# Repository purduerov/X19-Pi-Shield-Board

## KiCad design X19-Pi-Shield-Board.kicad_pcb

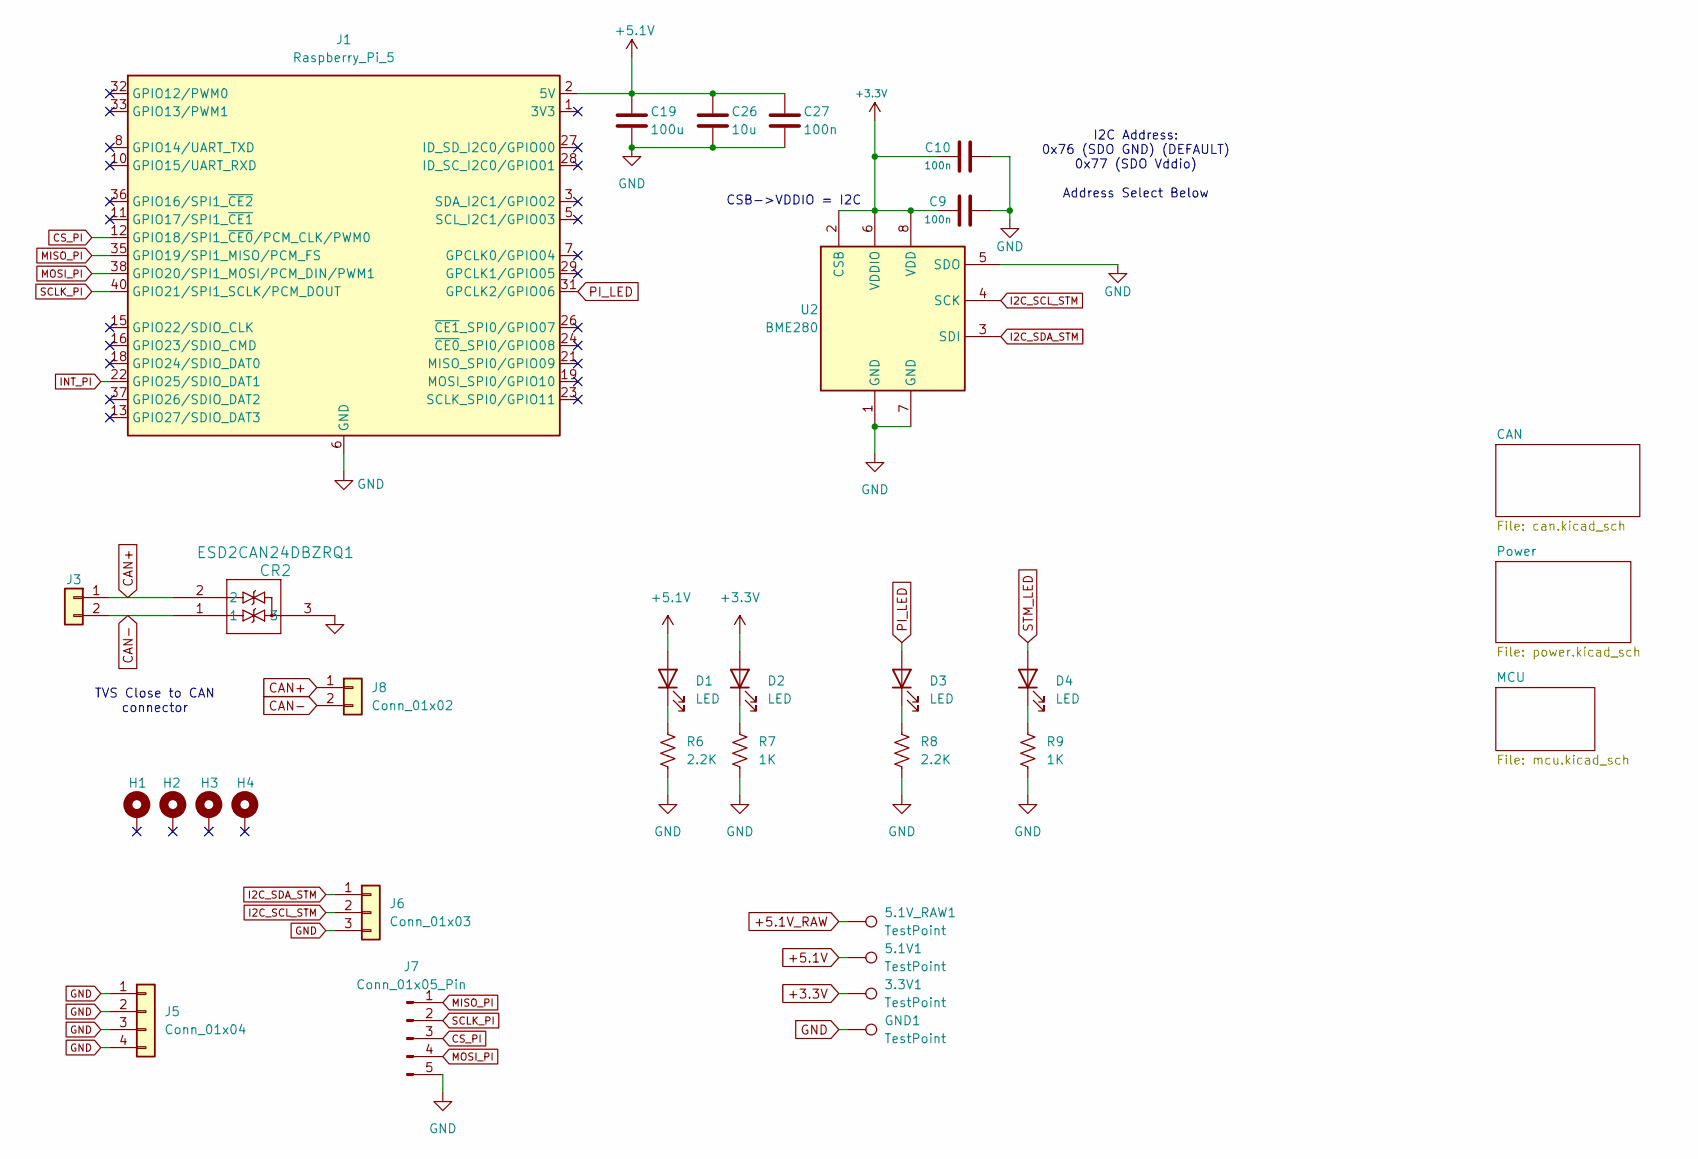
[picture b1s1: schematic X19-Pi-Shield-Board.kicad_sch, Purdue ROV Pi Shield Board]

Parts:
3.3V1, 5.1V1, 5.1V_RAW1: TestPoint; TestPoint_Pad_D2.5mm
C9, C10, C27: 100n; C_0603_1608Metric_Pad1.08x0.95mm_HandSolder
C19: 100u; PCAP_6.3x5.8-ELECT_NCA-M
C26: 10u; C_0603_1608Metric_Pad1.08x0.95mm_HandSolder
CR2: ESD2CAN24DBZRQ1; SOT-23_DBZ_TEX-M
D1, D2, D3, D4: LED; LED_0805_2012Metric_Pad1.15x1.40mm_HandSolder
GND1: TestPoint; TestPoint_Pad_D2.5mm
H1, H2, H3, H4: MountingHole_Pad; MountingHole_3.2mm_M3
J1: Raspberry_Pi_5; PinSocket_2x20_P2.54mm_Vertical
J3: Conn_01x02; CONN_SD-43650-001_02_MOL
J5: Conn_01x04; PinHeader_1x04_P2.54mm_Vertical
J6: Conn_01x03; PinHeader_1x03_P2.54mm_Vertical
J7: Conn_01x05_Pin; PinHeader_1x05_P2.54mm_Vertical
J8: Conn_01x02; PinHeader_1x02_P2.54mm_Vertical
R6, R8: 2.2K; R_0603_1608Metric_Pad0.98x0.95mm_HandSolder
R7, R9: 1K; R_0603_1608Metric_Pad0.98x0.95mm_HandSolder
U2: BME280; Bosch_LGA-8_2.5x2.5mm_P0.65mm_ClockwisePinNumbering

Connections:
+3.3V: 3.3V1.1 (1_1), C9.1, C10.2, D2.2 (A), U2.2 (CSB), U2.6 (VDDIO), U2.8 (VDD); also elsewhere on the board
+5.1V: 5.1V1.1 (1_1), C19.1, C26.1, C27.1, D1.2 (A), J1.2 (5V), J1.4 (5V); also elsewhere on the board
+5.1V_RAW: 5.1V_RAW1.1 (1_1); also elsewhere on the board
CAN+: CR2.2, J3.1, J8.1; also elsewhere on the board
CAN-: CR2.1, J3.2, J8.2; also elsewhere on the board
CS_PI: J1.12 (GPIO18/SPI1_~CE0/PCM_CLK/PWM0), J7.3; also elsewhere on the board
GND: C9.2, C10.1, C19.2, C26.2, C27.2, CR2.3, GND1.1 (1_1), J1.6 (GND), J1.9 (GND), J1.14 (GND), J1.20 (GND), J1.25 (GND), J1.30 (GND), J1.34 (GND), J1.39 (GND), J5.1, J5.2, J5.3, J5.4, J6.3, J7.5, R6.2, R7.2, R8.2, R9.2, U2.1 (GND), U2.5 (SDO), U2.7 (GND); also elsewhere on the board
I2C_SCL_STM: J6.2, U2.4 (SCK); also elsewhere on the board
I2C_SDA_STM: J6.1, U2.3 (SDI); also elsewhere on the board
INT_PI: J1.22 (GPIO25/SDIO_DAT1); also elsewhere on the board
MISO_PI: J1.35 (GPIO19/SPI1_MISO/PCM_FS), J7.1; also elsewhere on the board
MOSI_PI: J1.38 (GPIO20/SPI1_MOSI/PCM_DIN/PWM1), J7.4; also elsewhere on the board
unnamed: D1.1 (K), R6.1
unnamed: D2.1 (K), R7.1
unnamed: D3.1 (K), R8.1
unnamed: D4.1 (K), R9.1
PI_LED: D3.2 (A), J1.31 (GPCLK2/GPIO06)
SCLK_PI: J1.40 (GPIO21/SPI1_SCLK/PCM_DOUT), J7.2; also elsewhere on the board
STM_LED: D4.2 (A); also elsewhere on the board

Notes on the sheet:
CSB->VDDIO = I2C
TVS Close to CAN connector
I2C Address: 0x76 (SDO GND) (DEFAULT) 0x77 (SDO Vddio) Address Select Below

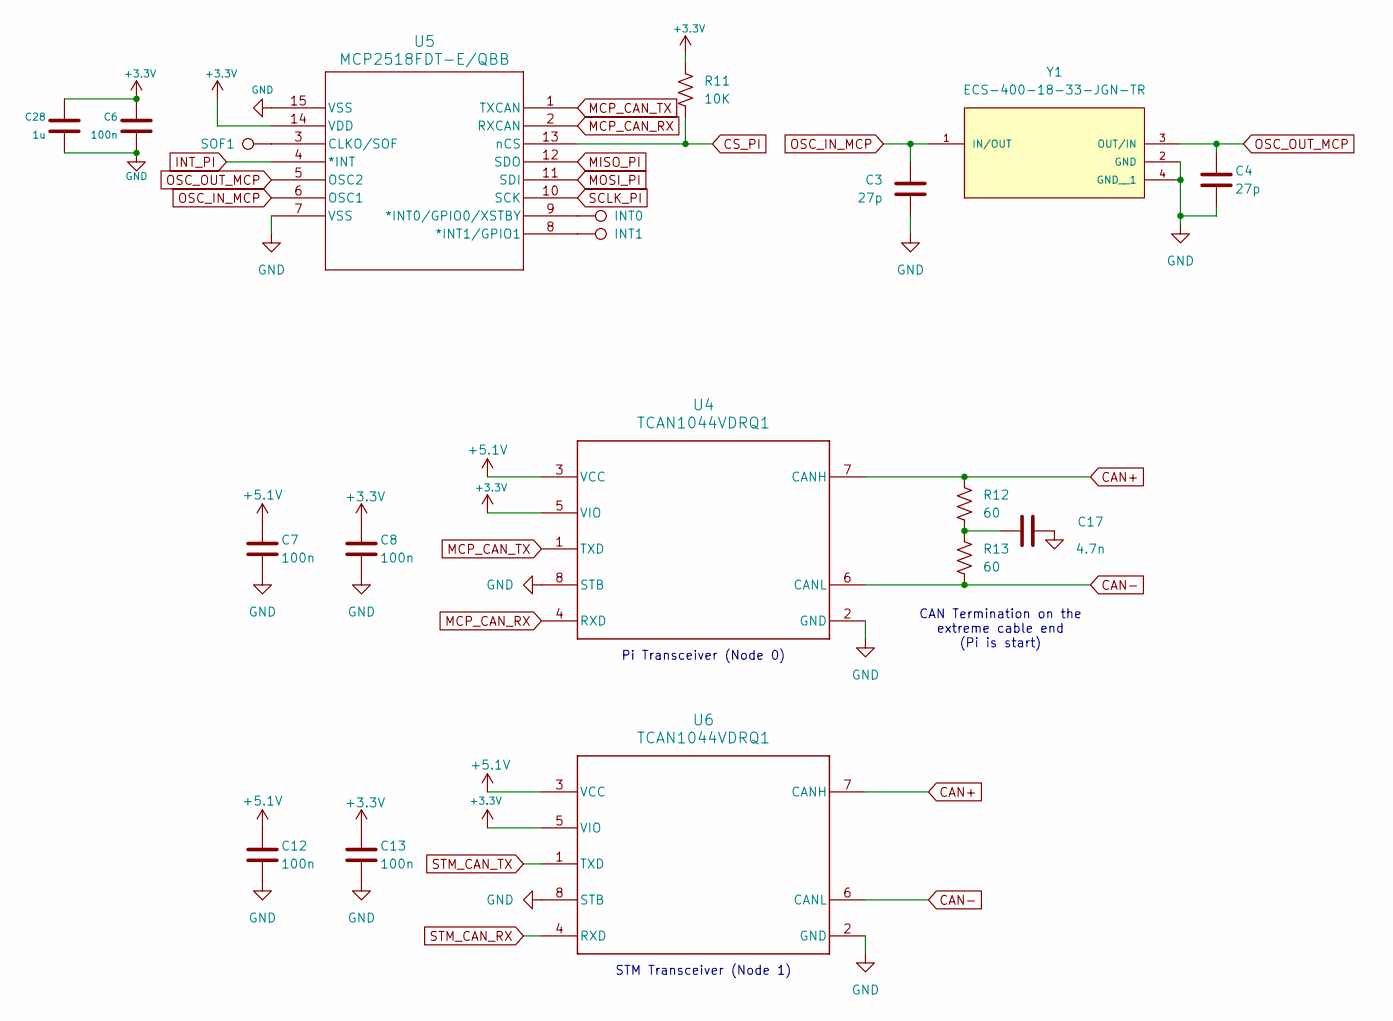
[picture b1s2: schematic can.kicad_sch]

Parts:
C3, C4: 27p; C_0603_1608Metric_Pad1.08x0.95mm_HandSolder
C6, C7, C8, C12, C13: 100n; C_0603_1608Metric_Pad1.08x0.95mm_HandSolder
C17: 4.7n; C_0603_1608Metric_Pad1.08x0.95mm_HandSolder
C28: 1u; C_0603_1608Metric_Pad1.08x0.95mm_HandSolder
INT0, INT1: TestPoint; TestPoint_Pad_D1.5mm
R11: 10K; R_0603_1608Metric_Pad0.98x0.95mm_HandSolder
R12, R13: 60; R_0603_1608Metric_Pad0.98x0.95mm_HandSolder
SOF1: TestPoint; TestPoint_Pad_D1.5mm
U4, U6: TCAN1044VDRQ1; D0008A-IPC_A
U5: MCP2518FDT-E/QBB; VDFN14_QBB_MCH-M
Y1: ECS-400-18-33-JGN-TR; XTAL_ECS-400-18-33-JGN-TR

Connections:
+3.3V: C6.1, C8.1, C13.1, C28.1, R11.1, U4.5 (VIO), U5.14 (VDD), U6.5 (VIO); also elsewhere on the board
+5.1V: C7.1, C12.1, U4.3 (VCC), U6.3 (VCC); also elsewhere on the board
CAN+: R12.1, U4.7 (CANH), U6.7 (CANH); also elsewhere on the board
CAN-: R13.2, U4.6 (CANL), U6.6 (CANL); also elsewhere on the board
CS_PI: R11.2, U5.13 (nCS); also elsewhere on the board
GND: C3.1, C4.2, C6.2, C7.2, C8.2, C12.2, C13.2, C17.2, C28.2, U4.2 (GND), U4.8 (STB), U5.7 (VSS), U5.15 (VSS), U6.2 (GND), U6.8 (STB), Y1.2 (GND), Y1.4 (GND__1); also elsewhere on the board
INT_PI: U5.4 (*INT); also elsewhere on the board
MCP_CAN_RX: U4.4 (RXD), U5.2 (RXCAN)
MCP_CAN_TX: U4.1 (TXD), U5.1 (TXCAN)
MISO_PI: U5.12 (SDO); also elsewhere on the board
MOSI_PI: U5.11 (SDI); also elsewhere on the board
unnamed: C17.1, R12.2, R13.1
unnamed: INT0.1 (1_1), U5.9 (*INT0/GPIO0/XSTBY)
unnamed: INT1.1 (1_1), U5.8 (*INT1/GPIO1)
unnamed: SOF1.1 (1_1), U5.3 (CLKO/SOF)
OSC_IN_MCP: C3.2, U5.6 (OSC1), Y1.1 (IN/OUT)
OSC_OUT_MCP: C4.1, U5.5 (OSC2), Y1.3 (OUT/IN)
SCLK_PI: U5.10 (SCK); also elsewhere on the board
STM_CAN_RX: U6.4 (RXD); also elsewhere on the board
STM_CAN_TX: U6.1 (TXD); also elsewhere on the board

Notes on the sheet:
CAN Termination on the extreme cable end (Pi is start)
Pi Transceiver (Node 0)
STM Transceiver (Node 1)

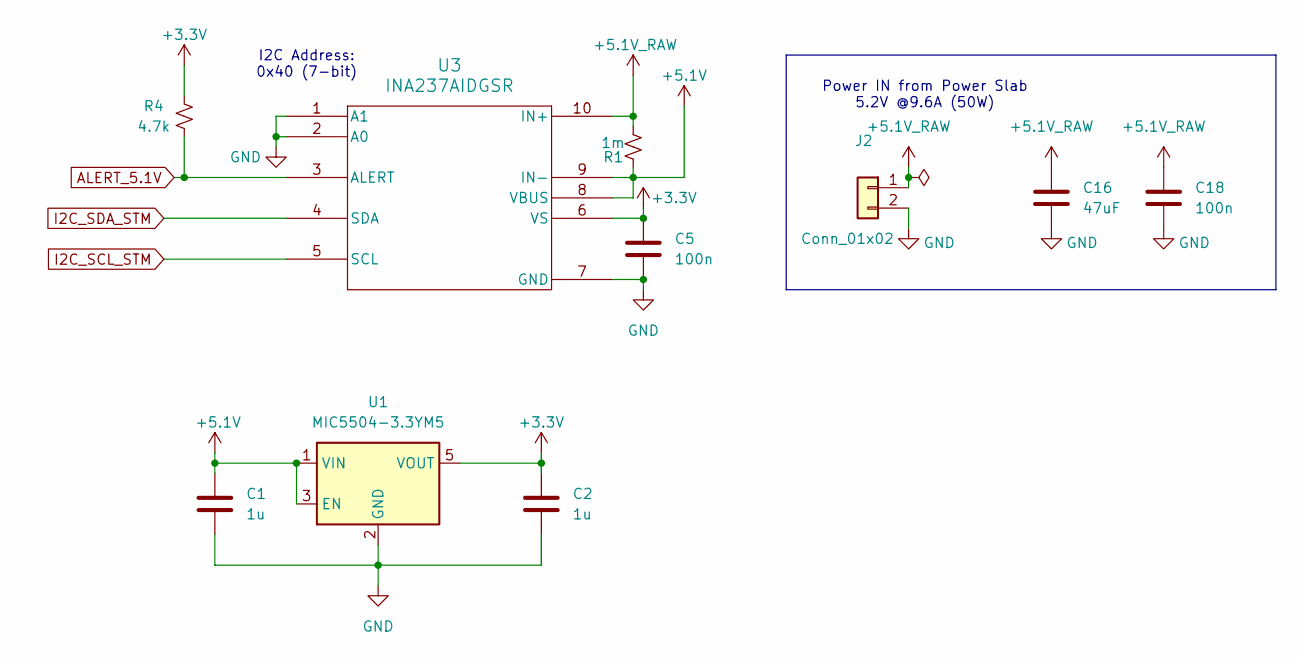
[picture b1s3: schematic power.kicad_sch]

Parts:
C1, C2: 1u; C_0603_1608Metric_Pad1.08x0.95mm_HandSolder
C5, C18: 100n; C_0603_1608Metric_Pad1.08x0.95mm_HandSolder
C16: 47uF; C_1210_3225Metric_Pad1.33x2.70mm_HandSolder
J2: Conn_01x02; CONN_SD-43650-001_02_MOL
R1: 1m; R_1206_3216Metric_Pad1.30x1.75mm_HandSolder
R4: 4.7k; R_0603_1608Metric_Pad0.98x0.95mm_HandSolder
U1: MIC5504-3.3YM5; SOT-23-5
U3: INA237AIDGSR; VSSOP_IDGSR_TEX-M

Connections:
+3.3V: C2.1, C5.1, R4.2, U1.5 (VOUT), U3.6 (VS); also elsewhere on the board
+5.1V: C1.1, R1.1, U1.1 (VIN), U1.3 (EN), U3.8 (VBUS), U3.9 (IN-); also elsewhere on the board
+5.1V_RAW: C16.1, C18.1, J2.1, R1.2, U3.10 (IN+); also elsewhere on the board
ALERT_5.1V: R4.1, U3.3 (ALERT); also elsewhere on the board
GND: C1.2, C2.2, C5.2, C16.2, C18.2, J2.2, U1.2 (GND), U3.1 (A1), U3.2 (A0), U3.7 (GND); also elsewhere on the board
I2C_SCL_STM: U3.5 (SCL); also elsewhere on the board
I2C_SDA_STM: U3.4 (SDA); also elsewhere on the board

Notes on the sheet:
I2C Address: 0x40 (7-bit)
Power IN from Power Slab 5.2V @9.6A (50W)

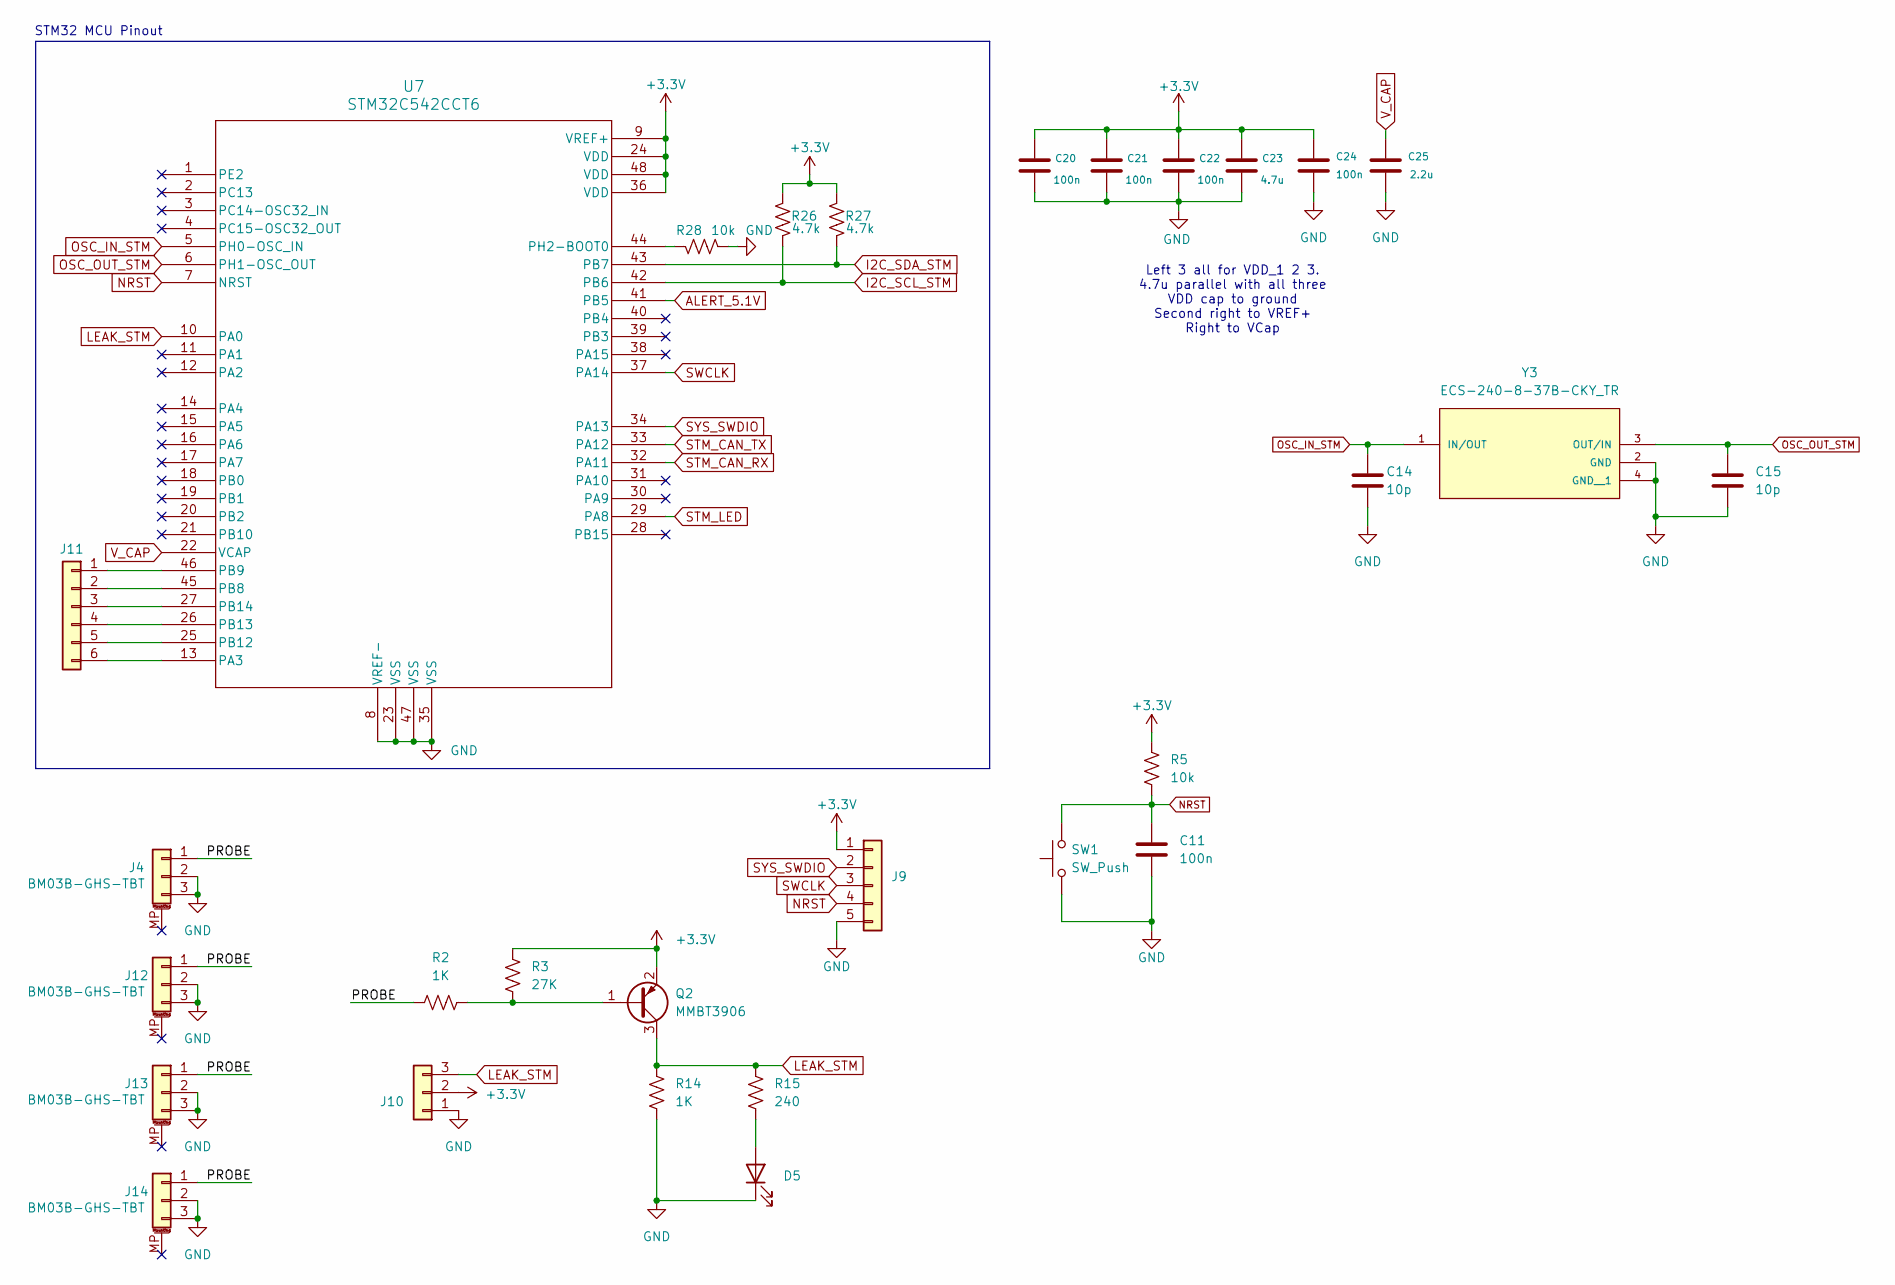
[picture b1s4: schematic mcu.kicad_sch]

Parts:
C11, C20, C21, C22, C24: 100n; C_0603_1608Metric_Pad1.08x0.95mm_HandSolder
C14, C15: 10p; C_0603_1608Metric_Pad1.08x0.95mm_HandSolder
C23: 4.7u; C_0603_1608Metric_Pad1.08x0.95mm_HandSolder
C25: 2.2u; C_0603_1608Metric_Pad1.08x0.95mm_HandSolder
D5: LED; LED_0805_2012Metric_Pad1.15x1.40mm_HandSolder
J4, J12, J13, J14: BM03B-GHS-TBT; JST_GH_BM03B-GHS-TBT_1x03-1MP_P1.25mm_Vertical
J9: Conn_01x05; PinHeader_1x05_P2.54mm_Vertical
J10: Conn_01x03; PinHeader_1x03_P2.54mm_Vertical
J11: Conn_01x06; PinHeader_1x06_P2.54mm_Vertical
Q2: MMBT3906; SOT-23
R2, R14: 1K; R_0603_1608Metric_Pad0.98x0.95mm_HandSolder
R3: 27K; R_0603_1608Metric_Pad0.98x0.95mm_HandSolder
R5, R28: 10k; R_0603_1608Metric_Pad0.98x0.95mm_HandSolder
R15: 240; R_0603_1608Metric_Pad0.98x0.95mm_HandSolder
R26, R27: 4.7k; R_0603_1608Metric_Pad0.98x0.95mm_HandSolder
SW1: SW_Push; SW_FSM2JMTR_TEC-M
U7: STM32C542CCT6; LQFP48-7X7-M
Y3: ECS-240-8-37B-CKY_TR; XTAL_ECS-160-9-37-CKM-TR

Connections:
+3.3V: C20.1, C21.1, C22.1, C23.1, C24.1, J9.1, J10.2, Q2.2 (E), R3.1, R5.1, R26.2, R27.2, U7.9 (VREF+), U7.24 (VDD), U7.36 (VDD), U7.48 (VDD); also elsewhere on the board
/MCU/PROBE: J4.1, J12.1, J13.1, J14.1, R2.1
ALERT_5.1V: U7.41 (PB5); also elsewhere on the board
GND: C11.2, C14.1, C15.2, C20.2, C21.2, C22.2, C23.2, C24.2, C25.2, D5.1 (K), J4.2, J4.3, J9.5, J10.1, J12.2, J12.3, J13.2, J13.3, J14.2, J14.3, R14.2, R28.1, SW1.1, U7.8 (VREF-), U7.23 (VSS), U7.35 (VSS), U7.47 (VSS), Y3.2 (GND), Y3.4 (GND__1); also elsewhere on the board
I2C_SCL_STM: R26.1, U7.42 (PB6); also elsewhere on the board
I2C_SDA_STM: R27.1, U7.43 (PB7); also elsewhere on the board
LEAK_STM: J10.3, Q2.3 (C), R14.1, R15.1, U7.10 (PA0)
NRST: C11.1, J9.4, R5.2, SW1.2, U7.7 (NRST)
unnamed: D5.2 (A), R15.2
unnamed: J11.1, U7.46 (PB9)
unnamed: J11.2, U7.45 (PB8)
unnamed: J11.3, U7.27 (PB14)
unnamed: J11.4, U7.26 (PB13)
unnamed: J11.5, U7.25 (PB12)
unnamed: J11.6, U7.13 (PA3)
unnamed: Q2.1 (B), R2.2, R3.2
unnamed: R28.2, U7.44 (PH2-BOOT0)
OSC_IN_STM: C14.2, U7.5 (PH0-OSC_IN), Y3.1 (IN/OUT)
OSC_OUT_STM: C15.1, U7.6 (PH1-OSC_OUT), Y3.3 (OUT/IN)
STM_CAN_RX: U7.32 (PA11); also elsewhere on the board
STM_CAN_TX: U7.33 (PA12); also elsewhere on the board
STM_LED: U7.29 (PA8); also elsewhere on the board
SWCLK: J9.3, U7.37 (PA14)
SYS_SWDIO: J9.2, U7.34 (PA13)
V_CAP: C25.1, U7.22 (VCAP)

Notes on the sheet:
STM32 MCU Pinout
Left 3 all for VDD_1 2 3. 4.7u parallel with all three VDD cap to ground Second right to VREF+ Right to VCap

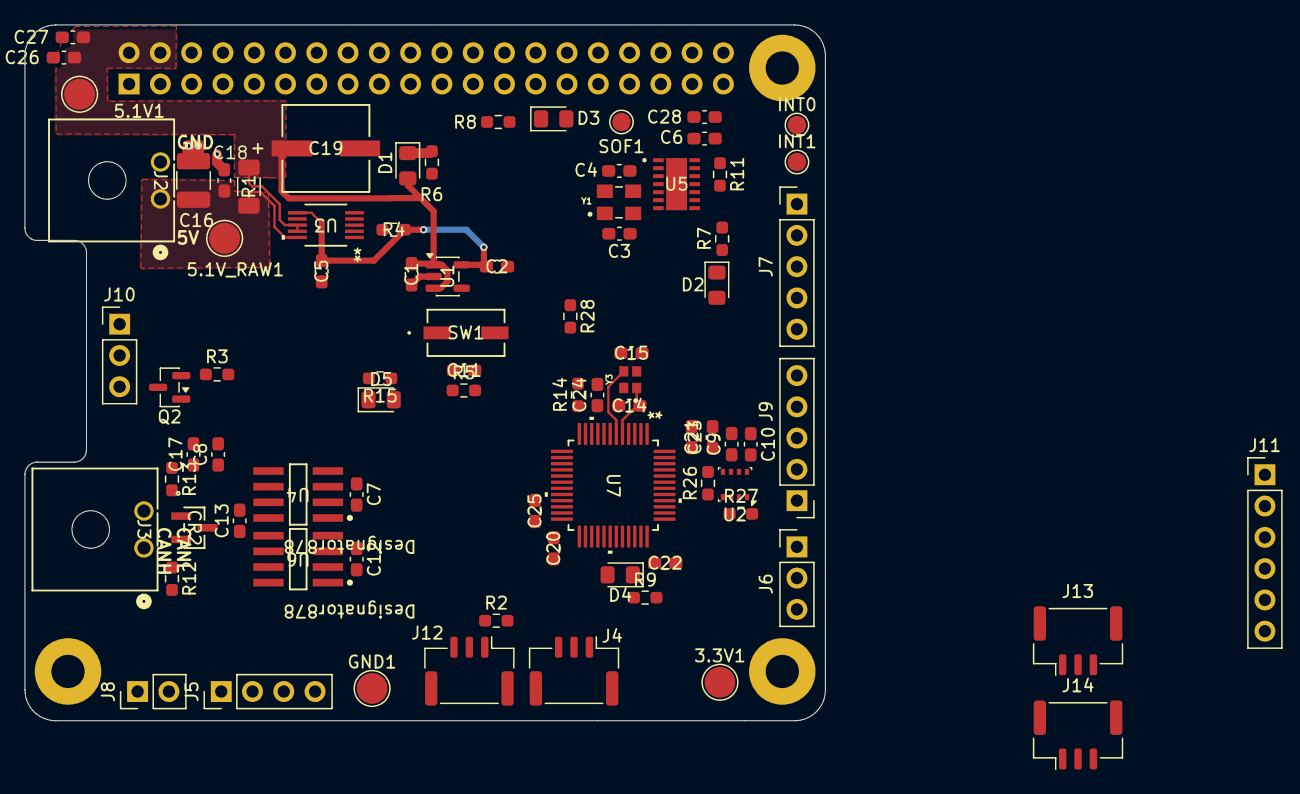
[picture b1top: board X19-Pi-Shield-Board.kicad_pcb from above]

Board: 4 copper layers, 65.0 x 56.5 mm, 86 parts (1 on the bottom side), 47 nets.

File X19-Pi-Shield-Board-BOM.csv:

Row,Description,Part,References,Value,Footprint,Quantity Per PCB,Status,Datasheet,digikey,Sim.Pins,MF,PACKAGE,PRICE,STANDARD,MP,AVAILABILITY
1,Unpolarized capacitor,C,C3 C4 C14 C15,27p,C_0603_1608Metric_Pad1.08x0.95mm_HandSolder,4, ,,,,,,,,,
2,Unpolarized capacitor,C,C17,4.7n,C_0603_1608Metric_Pad1.08x0.95mm_HandSolder,1, ,,,,,,,,,
3,Unpolarized capacitor,C,C5 C6 C7 C8 C9 C10 C11 C12 C13 C18 C20 C21 C22 C24 C27,100n,C_0603_1608Metric_Pad1.08x0.95mm_HandSolder,15, ,,,,,,,,,
4,Unpolarized capacitor,C,C1 C2,1u,SOIC-8_3.9x4.9mm_P1.27mm,2, ,,,,,,,,,
5,Unpolarized capacitor,C,C28,1u,C_0603_1608Metric_Pad1.08x0.95mm_HandSolder,1, ,,,,,,,,,
6,Unpolarized capacitor,C,C25,2.2u,C_0603_1608Metric_Pad1.08x0.95mm_HandSolder,1, ,,,,,,,,,
7,Unpolarized capacitor,C,C23,4.7u,C_0603_1608Metric_Pad1.08x0.95mm_HandSolder,1, ,,,,,,,,,
8,Unpolarized capacitor,C,C26,10u,C_0603_1608Metric_Pad1.08x0.95mm_HandSolder,1, ,,,,,,,,,
9,Unpolarized capacitor,C,C16,47uF,C_0805_2012Metric_Pad1.18x1.45mm_HandSolder,1, ,,,,,,,,,
10,Unpolarized capacitor,C,C19,470u,C_0603_1608Metric_Pad1.08x0.95mm_HandSolder,1, ,,,,,,,,,
11,,ESD2CAN24DBZRQ1,CR2,ESD2CAN24DBZRQ1,SOT-23_DBZ_TEX-M,1, ,ESD2CAN24DBZRQ1,,,,,,,,
12,Light emitting diode,LED,D1 D2 D3 D4,LED,LED_0805_2012Metric_Pad1.15x1.40mm_HandSolder,4, ,,,1=K 2=A,,,,,,
13,"Generic connector, single row, 01x02, script generated (kicad-library-utils/schlib/autogen/connector/)",Conn_01x02,J2 J3,Conn_01x02,0436500200,2, ,,,,,,,,,
14,"Generic connector, single row, 01x02, script generated (kicad-library-utils/schlib/autogen/connector/)",Conn_01x02,J8,Conn_01x02,DFN-14-1EP_3x4.5mm_P0.65mm_EP1.65x4.25mm,1, ,,,,,,,,,
15,"Generic connector, single row, 01x03, script generated (kicad-library-utils/schlib/autogen/connector/)",Conn_01x03,J6,Conn_01x03,Oscillator_SMD_ECS_2520MV-xxx-xx-4Pin_2.5x2.0mm,1, ,,,,,,,,,
16,"Generic connector, single row, 01x04, script generated (kicad-library-utils/schlib/autogen/connector/)",Conn_01x04,J5,Conn_01x04,Oscillator_SMD_ECS_2520MV-xxx-xx-4Pin_2.5x2.0mm,1, ,,,,,,,,,
17,"Generic connector, single row, 01x05, script generated (kicad-library-utils/schlib/autogen/connector/)",Conn_01x05,J9,Conn_01x05,PinHeader_1x05_P2.54mm_Horizontal,1, ,,,,,,,,,
18,"Generic connector, single row, 01x05, script generated",Conn_01x05_Pin,J7,Conn_01x05_Pin,PinHeader_1x05_P2.54mm_Horizontal,1, ,,,,,,,,,
19,"Generic connector, single row, 01x06, script generated (kicad-library-utils/schlib/autogen/connector/)",Conn_01x06,J4,Conn_01x06,PinHeader_1x06_P2.54mm_Horizontal,1, ,,,,,,,,,
20,Raspberry Pi 4 Model B,Raspberry_Pi_4,J1,Raspberry_Pi_4,PinHeader_2x20_P2.54mm_Vertical,1, ,https://datasheets.raspberrypi.com/rpi4/raspberry-pi-4-datas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,,,,,,,,
21,"Jumper, 2-pole, open",Jumper_2_Open,JP1,Jumper_2_Open,PinHeader_1x02_P2.54mm_Vertical,1, ,,,,,,,,,
22,"Resistor, small US symbol",R_Small_US,R1,1m,R_2512_6332Metric_Pad1.40x3.35mm_HandSolder,1, ,,,,,,,,,
23,"Resistor, US symbol",R_US,R12 R13,60,R_0603_1608Metric_Pad0.98x0.95mm_HandSolder,2, ,,,,,,,,,
24,"Resistor, US symbol",R_US,R7 R9,1K,R_0603_1608Metric_Pad0.98x0.95mm_HandSolder,2, ,,,,,,,,,
25,"Resistor, US symbol",R_US,R6 R8,2.2K,R_0603_1608Metric_Pad0.98x0.95mm_HandSolder,2, ,,,,,,,,,
26,"Resistor, US symbol",R_US,R26 R27,4.7k,R_0603_1608Metric_Pad0.98x0.95mm_HandSolder,2, ,,,,,,,,,
27,"Resistor, small US symbol",R_Small_US,R4,4.7k,R_0603_1608Metric_Pad0.98x0.95mm_HandSolder,1, ,,,,,,,,,
28,"Resistor, US symbol",R_US,R10 R11,10K,R_0603_1608Metric_Pad0.98x0.95mm_HandSolder,2, ,,,,,,,,,
29,"Resistor, US symbol",R_US,R5,10k,R_Array_SIP4,1, ,,,,,,,,,
30,"Push button switch, generic, two pins",SW_Push,SW1,SW_Push,SW_NKK_GW12LJP,1, ,,,,,,,,,
31,"3-in-1 sensor, humidity, pressure, temperature, I2C and SPI interface, 1.71-3.6V, LGA-8",BME280,U2,BME280,Bosch_LGA-8_2.5x2.5mm_P0.65mm_ClockwisePinNumbering,1, ,https://www.bosch-sensortec.com/media/boschsensortec/downloa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,,,,,,,,
32,,INA237AIDGSR,U3,INA237AIDGSR,VSSOP_IDGSR_TEX-M,1, ,https://www.ti.com/lit/gpn/ina237,,,,,,,,
33,,MCP2518FDT-E_QBB,U5,MCP2518FDT-E/QBB,VDFN14_QBB_MCH-M,1, ,MCP2518FDT-E/QBB,,,,,,,,
34,"300mA Low-dropout Voltage Regulator, Vout 3.3V, Vin up to 5.5V, SOT-23",MIC5504-3.3YM5,U1,MIC5504-3.3YM5,SOT-23-5,1, ,http://ww1.microchip.com/downloads/en/DeviceDoc/MIC550X.pdf,,,,,,,,
35,,STM32C542CCT6,U7,STM32C542CCT6,LQFP48-7X7-M,1, ,https://www.st.com/resource/en/datasheet/stm32c542cc.pdf,,,,,,,,
36,,TCAN1044VDRQ1,U4 U6,TCAN1044VDRQ1,D0008A-IPC_A,2, ,https://www.ti.com/lit/gpn/tcan1044-q1,,,,,,,,
37,The sub miniature ECX-32 is a compact SMD Crystal.,ECS-120-18-33-JGN-TR,Y1 Y3,ECS-400-18-33-JGN-TR,XTAL_ECS-120-18-33-JGN-TR,2, ,,,,ECS INC,SMD-4 ECX,,Manufacturer recommendations,ECX-32,Good





Project info:
Schematic:,X19-Pi-Shield-Board
Variant:,default
Revision:,
Date:,2026-10-16_20-10-38
KiCad Version:,10.0.5-unknown-202607221313~667fa36054~ubuntu25.10.1
Statistics:
Component Groups:,37
Component Count:,66
Fitted Components:,66
Number of PCBs:,1
Total Components:,66
